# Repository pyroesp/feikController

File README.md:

# feikController

feikController is a PIC16F18325 emulating a PlayStation 1 controller.  
I wanted to make this into a library but it's too device specific.    

## Disclaimer

This has been tested on my PlayStation 1 and it seems to be working fine.  
However, I am not responsible if for some reason your PlayStation gets damaged by using or installing this.  

You use this at your own risk.  

## Why

The original idea for feikController came from the fact you can use a second controller to play Time Crisis.  
You can use that second controller to hide/reload by pressing on the buttons with your foot, so it's just like the pedal button on the arcade games.  

I recently made the PlayStation 1 reset mod with the 16F18325 so I was confident I could emulate a controller.  

## Pedal project

The pedal project uses a pedal button to send an X button press to the PlayStation.  
Here's a demo of the pedal controller :  

You can find [a playlist](https://www.youtube.com/watch?v=J5fQKmc8AMY&list=PLGaX4WJGgdHhcbQUQQJR6zFgzyka-xVOa) of me struggling to make this pedal controller.  
  
Take a look at the source if you want to learn more about it. I've tried to add comments to the code.  

I'd like to point out that the code as it is now is overkill for just a pedal that only works for Time Crisis.  
**It's more a proof of concept on making a PlayStation 1 controller.**  

I also made it so you can use either normal open or normal close button with the pedal. You just need to change the button defines a bit, see the source files.

**Note:** You could very well use this 

## Schematic and PCB

The schematic and PCB is pretty much the same as the reset mod I did for the PlayStation 1, just a few changes and more pads for the button.  

## License

Attribution-ShareAlike 4.0 International, see license file for more info

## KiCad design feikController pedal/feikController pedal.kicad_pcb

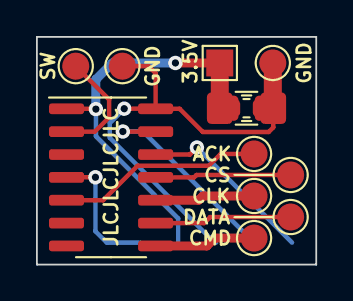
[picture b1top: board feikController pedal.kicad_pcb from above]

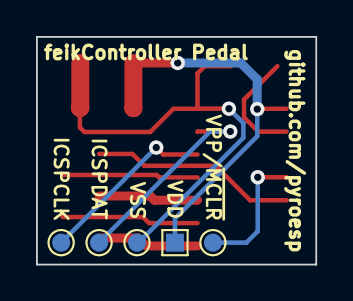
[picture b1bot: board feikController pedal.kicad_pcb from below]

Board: 2 copper layers, 15.5 x 12.6 mm, 18 parts (5 on the bottom side), 11 nets.

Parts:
3.5V: TestPoint; TestPoint_Pad_1.5x1.5mm
ACK: TestPoint; TestPoint_Pad_D1.5mm
C1: 0.1uF; C_1206_3216Metric_Pad1.42x1.75mm_HandSolder
C2: 0.1uF; C_0805_2012Metric_Pad1.15x1.40mm_HandSolder
C3: 0.1uF; C_0603_1608Metric_Pad1.05x0.95mm_HandSolder
CLK: TestPoint; TestPoint_Pad_D1.5mm
CMD: TestPoint; TestPoint_Pad_D1.5mm
CS: TestPoint; TestPoint_Pad_D1.5mm
DATA: TestPoint; TestPoint_Pad_D1.5mm
GND: TestPoint; TestPoint_Pad_D1.5mm
GND#2: TestPoint; TestPoint_Pad_D1.5mm
ICSPCLK: TestPoint; TestPoint_Pad_D1.0mm
ICSPDAT: TestPoint; TestPoint_Pad_D1.0mm
SW: TestPoint; TestPoint_Pad_D1.5mm
U1: PIC16F18325-ISL; SOIC-14_3.9x8.7mm_P1.27mm
VDD: TestPoint; TestPoint_Pad_1.0x1.0mm
VPP/~MCLR: TestPoint; TestPoint_Pad_D1.0mm
VSS: TestPoint; TestPoint_Pad_D1.0mm

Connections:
+3V3: 3.5V.1, C1.1, C2.1, C3.1, U1.1, VDD.1
/ACK: ACK.1, U1.5
/CLK: CLK.1, U1.10
/CMD: CMD.1, U1.8
/DATA: DATA.1, U1.9
/ICSPCLK: ICSPCLK.1, U1.12
/ICSPDAT: ICSPDAT.1, U1.13
/SW: SW.1, U1.2
/VPP\~MCLR: U1.4, VPP/~MCLR.1
/~SS: CS.1, U1.11
GND: C1.2, C2.2, C3.2, GND.1, GND#2.1, U1.14, VSS.1

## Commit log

2020-06-06 PIC configuration
2020-06-06 Playstation controller struct and settings
2020-06-06 Pedal settings
2020-06-06 main file
2020-06-07 updated readme and added license file
2020-07-05 updated links in readme
2020-07-05 moved ACK delay from interrupt and into main loop
2020-07-05 moved ACK from pedal to playstation and added playstation include
2020-07-05 fixed the code to not have to use a transistor on the DATA line
2020-07-13 updated code with bugfix and put in folder
2020-07-13 add gitignore to kicad project folder
2020-07-13 first commit kicad project
2020-12-26 updated schematic/PCB/gerber + added pics
2020-12-26 updated readme with pics
2021-01-17 general update/cleanup
